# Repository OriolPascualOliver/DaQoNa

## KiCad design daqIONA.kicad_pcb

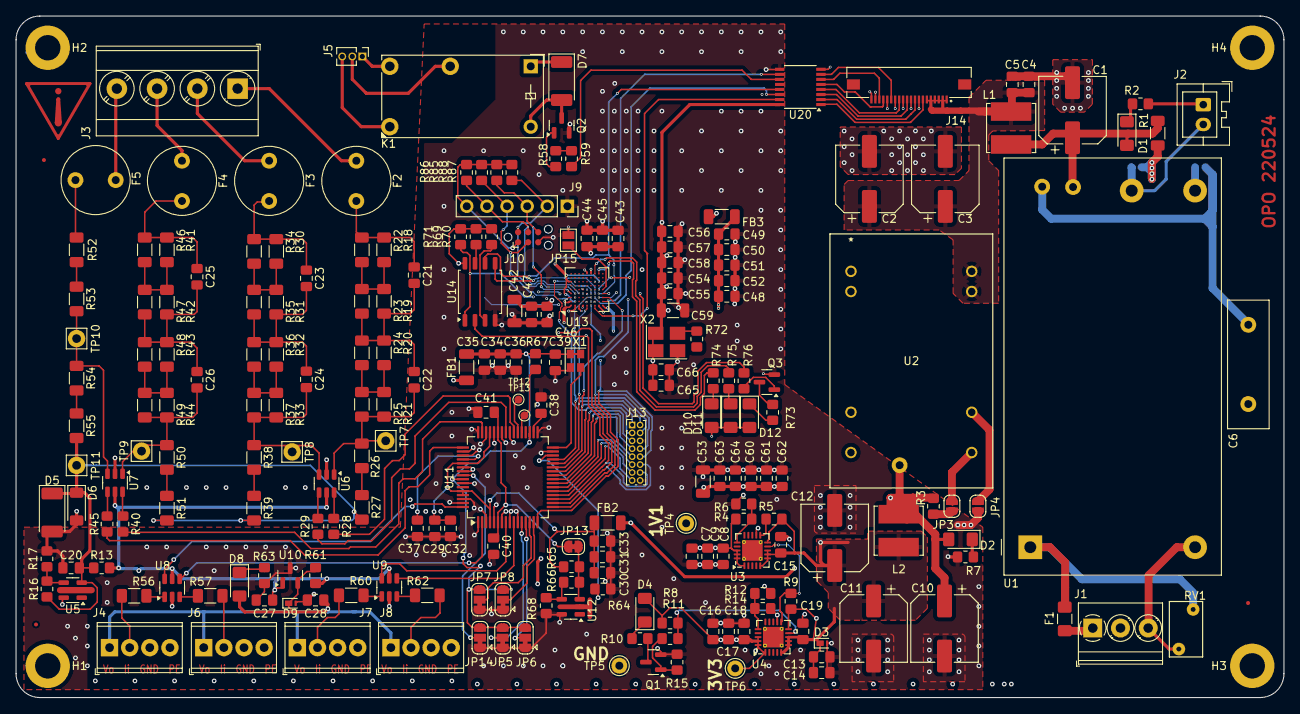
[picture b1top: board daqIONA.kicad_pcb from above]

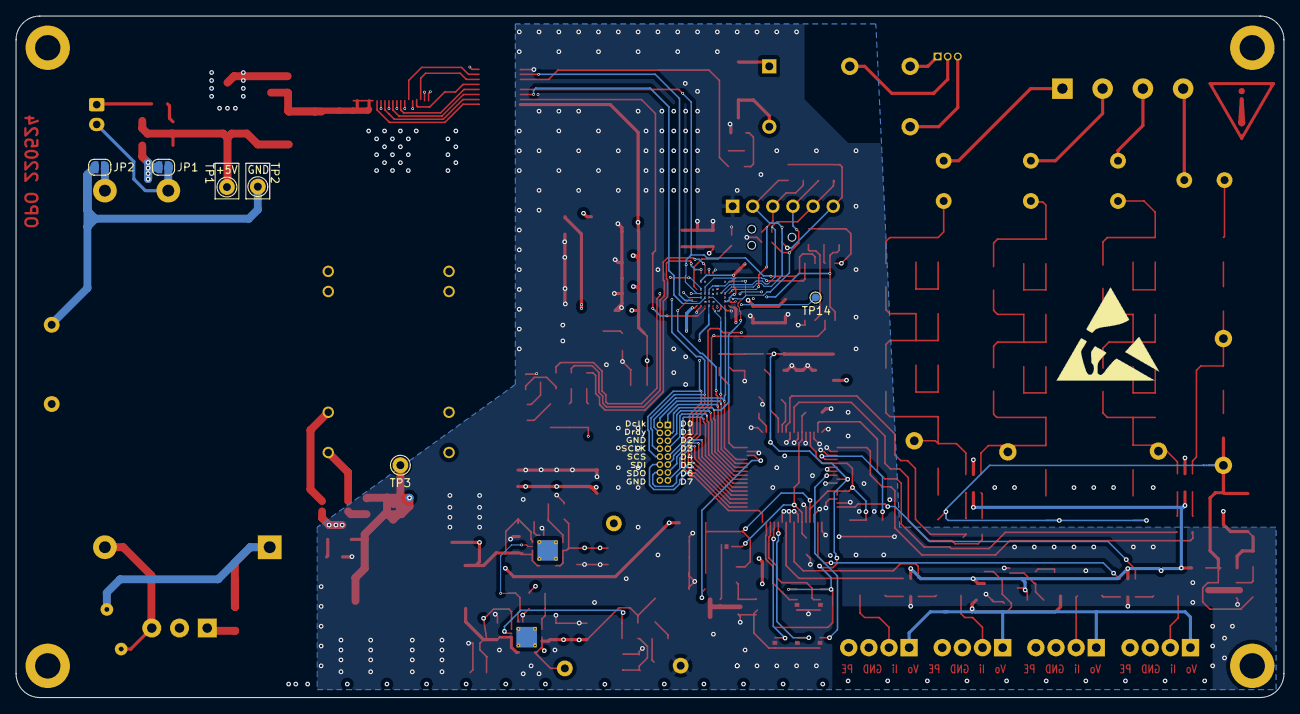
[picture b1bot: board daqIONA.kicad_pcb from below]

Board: 6 copper layers, 160.0 x 86.0 mm, 234 parts (6 on the bottom side), 144 nets.

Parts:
C1, C2, C3, C10, C11, C12: 220u; CP_Elec_8x6.9
C4, C7, C8, C13, C16, C17, C27, C28, C29, C30, C31, C34, C35, C39, C41, C44, C45, C49, C55, C56, C61, C62, C65, C66: 100n; C_0805_2012Metric_Pad1.18x1.45mm_HandSolder
C5, C14: 1n; C_0805_2012Metric_Pad1.18x1.45mm_HandSolder
C6: Cy; C_Disc_D16.0mm_W5.0mm_P10.00mm
C9, C15, C18, C19, C38: 10u; C_0805_2012Metric_Pad1.18x1.45mm_HandSolder
C20, C46, C47, C57, C58, C63, C64: 10n; C_0805_2012Metric_Pad1.18x1.45mm_HandSolder
C21, C22, C23, C24, C25, C26: 10p; C_0805_2012Metric_Pad1.18x1.45mm_HandSolder
C32, C33, C36, C37, C40, C43, C50, C51, C52, C54, C60: 1u; C_0805_2012Metric_Pad1.18x1.45mm_HandSolder
C42, C53, C59: 47u; C_1206_3216Metric
C48: 10nF; C_0805_2012Metric_Pad1.18x1.45mm_HandSolder
D1, D2, D4, D8, D10, D11, D12: LED; LED_1206_3216Metric_Pad1.42x1.75mm_HandSolder
D3: PTVS5V0Z1USK; Nexperia_DSN1608-2_1.6x0.8mm
D5, D7: D; D_MELF
D6: BZV55B2V4; D_MiniMELF
D9: PTVS7V5Z1USK; Nexperia_DSN1608-2_1.6x0.8mm
F1: Fuse; Fuse_1206_3216Metric_Pad1.42x1.75mm_HandSolder
F2, F3, F4, F5: Fuse; Fuse_Littelfuse_372_D8.50mm
FB1, FB2, FB3: FerriteBead_Small; L_1206_3216Metric_Pad1.22x1.90mm_HandSolder
FID1, FID2, FID3: Fiducial; Fiducial_0.5mm_Mask1mm
H1, H2, H3, H4: MountingHole_Pad; MountingHole_3.2mm_M3_DIN965_Pad
J1: AC PWR IN; TerminalBlock_Phoenix_PT-1,5-3-3.5-H_1x03_P3.50mm_Horizontal
J2: 5V FAN; JST_XA_B02B-XASK-1_1x02_P2.50mm_Vertical
J3: AC V MEAS; TerminalBlock_Phoenix_MKDS-3-4-5.08_1x04_P5.08mm_Horizontal
J4: Curr1 Meas; TerminalBlock_Phoenix_MPT-0,5-4-2.54_1x04_P2.54mm_Horizontal
J5: Relay OUT; PinHeader_1x03_P1.27mm_Vertical
J6: Curr2 Meas; TerminalBlock_Phoenix_MPT-0,5-4-2.54_1x04_P2.54mm_Horizontal
J7: Curr3 Meas; TerminalBlock_Phoenix_MPT-0,5-4-2.54_1x04_P2.54mm_Horizontal
J8: Curr4 Meas; TerminalBlock_Phoenix_MPT-0,5-4-2.54_1x04_P2.54mm_Horizontal
J9: Conn_01x06_Pin; PinSocket_1x06_P2.54mm_Vertical
J10: Conn_ARM_SWD_TagConnect_TC2030; Tag-Connect_TC2030-IDC-NL_2x03_P1.27mm_Vertical
J13: Conn_02x08_Odd_Even; PinHeader_2x08_P1.00mm_Vertical
J14: 687120183722
JP1, JP2, JP3, JP4: SolderJumper_2_Open; SolderJumper-2_P1.3mm_Open_RoundedPad1.0x1.5mm
JP5, JP6, JP7, JP8, JP14: SolderJumper_3_Bridged12; SolderJumper-3_P1.3mm_Bridged12_RoundedPad1.0x1.5mm
JP13: SolderJumper_2_Bridged; SolderJumper-2_P1.3mm_Bridged_RoundedPad1.0x1.5mm
JP15: RST; SolderJumper-2_P1.3mm_Open_Pad1.0x1.5mm
K1: Relay_SPDT; Relay_SPDT_Finder_32.21-x000
L1, L2: 2u2; L_Bourns_SRN6045TA
Q1, Q2, Q3: BC847; SOT-23
R1, R18, R19, R20, R21, R22, R23, R24, R25, R26, R27, R30, R31, R32, R33, R34, R35, R36, R37, R38, R39, R41, R42, R43, R44, R46, R47, R48, R49, R50, R51, R52, R53, R54, R55: R; R_1206_3216Metric_Pad1.30x1.75mm_HandSolder
R2, R7, R10, R58, R59, R63, R67, R73: 1K; R_0805_2012Metric_Pad1.20x1.40mm_HandSolder
R3, R16: 0R; R_0805_2012Metric_Pad1.20x1.40mm_HandSolder
R4: 1K87,1%; R_0805_2012Metric_Pad1.20x1.40mm_HandSolder
R5, R8, R11, R15: 10K; R_0805_2012Metric_Pad1.20x1.40mm_HandSolder
R6: 4K99,1%; R_0805_2012Metric_Pad1.20x1.40mm_HandSolder
R9, R76: 100K; R_0805_2012Metric_Pad1.20x1.40mm_HandSolder
R12: 3K57,1%; R_0805_2012Metric_Pad1.20x1.40mm_HandSolder
R13: 100R; R_0805_2012Metric_Pad1.20x1.40mm_HandSolder
R14: 1K15,1%; R_0805_2012Metric_Pad1.20x1.40mm_HandSolder
R17, R68: 300R; R_0805_2012Metric_Pad1.20x1.40mm_HandSolder
R28, R29, R40, R45: 50R; R_0805_2012Metric_Pad1.20x1.40mm_HandSolder
R56, R57, R60, R62: 1K; R_1206_3216Metric_Pad1.30x1.75mm_HandSolder
R61: 1R; R_0805_2012Metric_Pad1.20x1.40mm_HandSolder
R64: DNI; R_0805_2012Metric_Pad1.20x1.40mm_HandSolder
R65: 15R; R_0805_2012Metric_Pad1.20x1.40mm_HandSolder
R66: 190R; R_0805_2012Metric_Pad1.20x1.40mm_HandSolder
R69, R70, R71: 10k; R_0805_2012Metric_Pad1.20x1.40mm_HandSolder
R72: 33R; R_0805_2012Metric_Pad1.20x1.40mm_HandSolder
R74, R75: 1k; R_0805_2012Metric_Pad1.20x1.40mm_HandSolder
R85, R86, R87, R88: 5k; R_0805_2012Metric_Pad1.20x1.40mm_HandSolder
RV1: Varistor; RV_Disc_D7mm_W4.2mm_P5mm
TP1: 5VA; Pin_D1.0mm_L10.0mm
TP2: GND; Pin_D1.0mm_L10.0mm
TP3: 5VB; Pin_D1.0mm_L10.0mm
TP4: 1V1; Pin_D1.0mm_L10.0mm
TP5: GND3; Pin_D1.0mm_L10.0mm
TP6: 3V3; Pin_D1.0mm_L10.0mm
TP7: L1_lv; Pin_D1.1mm_L8.5mm_W2.5mm_FlatFork
TP8: L2_lv; Pin_D1.1mm_L8.5mm_W2.5mm_FlatFork
TP9: L3_lv; Pin_D1.1mm_L8.5mm_W2.5mm_FlatFork
TP10: N-lv; Pin_D1.1mm_L8.5mm_W2.5mm_FlatFork
TP11: lv_ref; Pin_D1.1mm_L8.5mm_W2.5mm_FlatFork
TP12, TP13: TestPoint; TestPoint_Pad_D1.0mm
TP14: NSTATUS; TestPoint_Pad_D1.0mm
U1: IRM-20-5; Converter_ACDC_MeanWell_IRM-20-xx_THT
U2: REC5A-0505SW/H2; DIP24_31.8X20.3X10.2_RCP
U3, U4: NCP59744; MLF-20-1EP_4x4mm_P0.5mm_EP2.6x2.6mm_ThermalVias
U5, U12: TL431DBV; SOT-23-5
U6, U7, U8, U9: USBLC6-2SC6; SOT-23-6
U10: RT9742SNGV; SOT-23
U11: AD7768BSTZ; LQFP-64_10x10mm_P0.5mm
U13: T8F81C2; BGA-81_5x5mm_Layout9x9_P0.5mm_Ball0.25mm_Pad0.2mm_NSMD
U14: W25Q128JVS; SOIC-8_5.23x5.23mm_P1.27mm
U20: ISO7761FDBQ; SSOP-16_3.9x4.9mm_P0.635mm
X1: SG-210STF; Oscillator_SMD_SeikoEpson_SG210-4Pin_2.5x2.0mm
X2: ASE-33.333MHZ-LC-T; Oscillator_SMD_Abracon_ASE-4Pin_3.2x2.5mm_HandSoldering

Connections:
+1V1: C7.1, C8.1, C9.1, C42.1, C43.1, C44.1, C45.1, C46.1, C47.1, FB3.1, R4.2, TP4.1, U3.1 (OUT), U3.18 (OUT), U3.19 (OUT), U3.20 (OUT), U13.C1 (VCC), U13.D4 (VCC), U13.E5 (VCC), U13.F2 (VCC), U13.F9 (VCC)
+3V3: C16.1, C17.1, C18.1, C53.1, C54.1, C55.1, C56.1, C57.1, C58.1, C59.1, C60.1, C61.1, C62.1, C63.1, C64.1, C65.1, C66.1, D4.2 (A), D10.2 (A), D11.2 (A), D12.2 (A), FB1.1, J9.6, J10.1 (VCC), R8.1, R12.2, R69.1, R70.1, R71.1, R85.1, R86.1, R87.1, R88.1, TP6.1, U4.1 (OUT), U4.18 (OUT), U4.19 (OUT), U4.20 (OUT), U13.A7 (VCCIO2A), U13.B2 (VCCIO1B), U13.H7 (VCCIO2B), U13.J1 (VCCIO1A), U14.8 (VCC), U20.16 (Vcc2), X2.1 (EN), X2.4 (Vdd)
+5V: C2.1, C3.1, C4.1, C5.1, J14.1, J14.2, J14.3, J14.4, J14.5, J14.6, L1.2, U2.22 (Vi+), U2.23 (Vi+)
+5VA: C11.1, C12.1, C13.1, C14.1, C15.1, C19.1, C27.1, D3.1 (K), D7.1 (K), FB2.2, K1.A1, L2.2, R5.2, R9.2, R13.1, R61.2, U3.5 (IN), U3.6 (IN), U3.7 (IN), U3.8 (IN), U3.10 (BIAS), U4.5 (IN), U4.6 (IN), U4.7 (IN), U4.8 (IN), U4.10 (BIAS), U6.5 (VBUS), U7.5 (VBUS), U8.5 (VBUS), U9.5 (VBUS), U10.1 (IN)
/(1) Power Supply/5V_PSU: J2.2, JP1.1 (A), U1.4 (+Vo)
/(1) Power Supply/Fb_{1V1}: R4.1, R6.2, U3.16 (FB)
/(1) Power Supply/Fb_{3V3}: R12.1, R14.2, U4.16 (FB)
/(1) Power Supply/PG: R8.2, R11.2, U4.9 (PG)
/(1) Power Supply/PWR_EN: R9.1, U3.9 (PG), U4.11 (EN)
/(2) Front End/Ext5V: C28.1, D8.2 (A), D9.1 (K), J4.1, J6.1, J7.1, J8.1, R61.1, U10.2 (OUT)
/(2) Front End/I1: R56.2, U8.1 (I/O1)
/(2) Front End/I2: R57.2, U8.3 (I/O2)
/(2) Front End/I3: R60.2, U9.1 (I/O1)
/(2) Front End/I4: R62.2, U9.3 (I/O2)
/(2) Front End/L1: F2.1, J3.1
/(2) Front End/L1_LV: C22.2, R21.2, R25.2, R26.1, TP7.1, U6.1 (I/O1)
/(2) Front End/L2: F3.1, J3.2
/(2) Front End/L2_LV: C24.2, R33.2, R37.2, R38.1, TP8.1, U6.3 (I/O2)
/(2) Front End/L3: F4.1, J3.3
/(2) Front End/L3_LV: C26.2, R44.2, R49.2, R50.1, TP9.1, U7.1 (I/O1)
/(2) Front End/N: F5.2, J3.4
/(2) Front End/N_LV: R53.2, R54.1, TP10.1, U7.3 (I/O2)
/(3) ADC/MODE0: JP5.2 (C), U11.12 (MODE0/GPIO0)
/(3) ADC/MODE1: JP6.2 (C), U11.13 (MODE1/GPIO1)
/(3) ADC/MODE2: JP7.2 (C), U11.14 (MODE2/GPIO2)
/(3) ADC/MODE3: JP8.2 (C), U11.15 (MODE3/GPIO3)
/(3) ADC/XTAL2: U11.32 (XTAL2/MCLK), X1.3 (OUT)
/(4) FPGA/CDONE: R76.2, U13.H5 (CDONE)
/(4) FPGA/CRST_B: JP15.2 (B), U13.J5 (CRESET_N)
/(4) FPGA/CS: U13.G1 (GPIOL_12_CTRL0), U20.15 (OUTA)
/(4) FPGA/Ext_AUX: J14.17, U20.5 (IND)
/(4) FPGA/Ext_RELAY: J14.18, U20.6 (INE)
/(4) FPGA/FPGA_HOLD: R69.2, U14.7 (IO3)
/(4) FPGA/FPGA_SS: R71.2, U13.J4 (GPIOL_01_SS_N), U14.1 (~CS)
/(4) FPGA/FPGA_TCK: J9.5, J10.4 (SWCLK), R86.2, U13.C4 (TCK)
/(4) FPGA/FPGA_TDI: J9.4, J10.3 (~RESET), R85.2, U13.A3 (TDI)
/(4) FPGA/FPGA_TDO: J9.3, J10.6 (SWO), R88.2, U13.A4 (TDO)
/(4) FPGA/FPGA_TMS: J9.2, J10.2 (SWDIO), R87.2, U13.B4 (TMS)
/(4) FPGA/FPGA~LD1: R74.2, U13.H9 (GPIOR_27)
/(4) FPGA/FPGA~LD2: R75.2, U13.G9 (GPIOR_26_CBSEL0)
/(4) FPGA/MISO: U13.J2 (GPIOL_09_CDI2), U20.10 (INF)
/(4) FPGA/MOSI: U13.G3 (GPIOL_07_CDI6), U20.14 (OUTB)
/(4) FPGA/RPI_3V3: J14.7, U20.1 (Vcc1)
/(4) FPGA/SPI0_MISO: J14.15, U20.7 (OUTF)
/(4) FPGA/SPI0_MOSI: J14.11, U20.3 (INB)
/(4) FPGA/SPI0_SCLK: J14.13, U20.4 (INC)
/(4) FPGA/SPI0_~CS: J14.9, U20.2 (INA)
/(4) FPGA/VCCA: C48.1, C49.1, C50.1, C51.1, C52.1, FB3.2, U13.A1 (VCCA_PLL)
AVDD: C29.1, C30.1, C31.1, C32.1, C33.1, FB2.1, R65.1, U11.4 (AVDD1A), U11.45 (AVDD1B), U11.53 (AVDD2B), U11.60 (AVDD2A), U11.61 (REGCAPA)
DCLK: J13.2, U11.28 (DCLK), U13.E1 (GPIOL_15_CLK1)
DOUT0: J13.1, U11.27 (DOUT0), U13.J3 (GPIOL_05_CDI5)
DOUT1: J13.3, U11.26 (DOUT1), U13.F4 (GPIOL_04_CDI0)
DOUT2: J13.5, U11.25 (DOUT2)
DOUT3: J13.7, U11.24 (DOUT3)
DOUT4: J13.9, U11.23 (DOUT4)
DOUT5: J13.11, U11.22 (DOUT5)
DOUT6: J13.13, U11.21 (DOUT6)
DOUT7: J13.15, U11.20 (DOUT7)
GND: C1.2, C2.2, C3.2, C4.2, C5.2, C6.1, J2.1, J14.8, J14.10, J14.12, J14.14, J14.16, J14.19, J14.20, JP2.2 (B), R2.2, TP2.1, U2.2 (Vi-), U2.3 (Vi-), U20.8 (GND1)
GND2: JP2.1 (A), U1.3 (-Vo)
GND3: C6.2, C7.2, C8.2, C9.2, C10.2, C11.2, C12.2, C13.2, C14.2, C15.2, C16.2, C17.2, C18.2, C19.2, C20.2, C27.2, C28.2, C29.2, C30.2, C31.2, C32.2, C33.2, C34.2, C35.2, C36.2, C37.1, C38.1, C39.2, C40.2, C41.2, C42.2, C43.2, C44.2, C45.2, C46.2, C47.2, C48.2, C49.2, C50.2, C51.2, C52.2, C53.2, C54.2, C55.2, C56.2, C57.2, C58.2, C59.2, C60.2, C61.2, C62.2, C63.2, C64.2, C65.2, C66.2, D3.2 (A), D5.2 (A), D6.2 (A), D9.2 (A), J4.3, J6.3, J7.3, J8.3, J9.1, J10.5 (GND), J13.6, J13.16, JP4.2 (B), JP5.1 (A), JP6.1 (A), JP7.1 (A), JP8.1 (A), JP14.1 (A), JP15.1 (A), Q1.2 (E), Q2.2 (E), Q3.2 (E), R6.1, R7.2, R14.1, R15.2, R17.2, R63.1, R64.1, R68.2, TP5.1, U3.12 (GND), U3.21, U4.12 (GND), U4.21, U5.5 (A), U6.2 (GND), U7.2 (GND), U8.2 (GND), U9.2 (GND), U10.3 (GND), U11.1 (AIN1-), U11.3 (AVSS1A), U11.5 (REF1-), U11.7 (AIN2-), U11.9 (AIN3-), U11.11 (FILTER/GPIO4), U11.31 (XTAL1), U11.33 (DGND), U11.40 (AIN7-), U11.42 (AIN6-), U11.44 (REF2-), U11.46 (AVSS1B), U11.48 (AIN5-), U11.50 (AIN4-), U11.51 (AVSS2B), U11.54 (AVSS), U11.55 (FORMAT1), U11.58 (CLK_SEL), U11.62 (AVSS2A), U11.63 (AIN0-), U12.5 (A), U13.A2 (GND), U13.B1 (GND), U13.B7 (GND), U13.D1 (GND), U13.D5 (GND), U13.E4 (GND), U13.E9 (GND), U13.G2 (GND), U13.G7 (GND), U13.H1 (GND), U14.4 (GND), U20.9 (GND2), X1.2 (GND), X2.2 (GND)
GNDS: C20.1, D5.1 (K), D6.1 (K), R13.2, R16.1, R27.2, R39.2, R51.2, R55.2, TP11.1, U5.3 (K)
I1_sense: U8.6 (I/O1), U11.64 (AIN0+)
I2_sense: U8.4 (I/O2), U11.2 (AIN1+)
I3_sense: U9.6 (I/O1), U11.8 (AIN2+)
I4_sense: U9.4 (I/O2), U11.10 (AIN3+)
IODD: C34.1, C35.1, C36.1, C39.1, FB1.2, JP5.3 (B), JP6.3 (B), JP7.3 (B), JP8.3 (B), JP14.3 (B), R67.2, U11.35 (IOVDD), U11.57 (~PIN/SPI), X1.1 (~ST), X1.4 (Vcc)
L1_sense: R28.2, U11.39 (AIN7+)
L2_sense: R29.2, U11.41 (AIN6+)
L3_sense: R40.2, U11.47 (AIN5+)
N_sense: R45.2, U11.49 (AIN4+)
unnamed: C21.1, F2.2, R18.1, R22.1
unnamed: C21.2, C22.1, R19.2, R20.1, R23.2, R24.1
unnamed: C23.1, F3.2, R30.1, R34.1
unnamed: C23.2, C24.1, R31.2, R32.1, R35.2, R36.1
unnamed: C25.1, F4.2, R41.1, R46.1
unnamed: C25.2, C26.1, R42.2, R43.1, R47.2, R48.1
unnamed: C1.1, D1.2 (A), L1.1, R1.2, TP1.1
unnamed: D1.1 (K), R2.1
unnamed: C10.1, D2.2 (A), L2.1, R3.2, TP3.1
unnamed: D2.1 (K), R7.1
unnamed: D4.1 (K), R10.1
unnamed: D7.2 (A), K1.A2, Q2.3 (C)
unnamed: D8.1 (K), R63.2
unnamed: D10.1 (K), R74.1
unnamed: D11.1 (K), R75.1
unnamed: D12.1 (K), R73.1
unnamed: F5.1, R52.1
unnamed: F1.1, J1.1
unnamed: J1.3, RV1.1, U1.2 (AC/N)
unnamed: J4.2, R56.1
unnamed: J5.1, K1.14
unnamed: J5.2, K1.11
unnamed: J5.3, K1.12
unnamed: J6.2, R57.1
unnamed: J7.2, R60.1
unnamed: J8.2, R62.1
unnamed: JP1.2 (B), R1.1
unnamed: JP3.1 (A), U2.14 (+Vo)
unnamed: JP3.2 (B), R3.1
unnamed: JP4.1 (A), U2.16 (-Vo)
unnamed: JP13.1 (A), R65.2, R66.1, U12.3 (K)
unnamed: JP14.2 (C), U11.56 (FORMAT0)
unnamed: Q1.1 (B), R11.1, R15.1
unnamed: Q1.3 (C), R10.2
unnamed: Q2.1 (B), R58.1
unnamed: Q3.1 (B), R76.1
unnamed: Q3.3 (C), R73.2
unnamed: R18.2, R19.1, R22.2, R23.1
unnamed: R20.2, R21.1, R24.2, R25.1
unnamed: R26.2, R27.1
unnamed: R28.1, U6.6 (I/O1)
unnamed: R29.1, U6.4 (I/O2)
unnamed: R30.2, R31.1, R34.2, R35.1
unnamed: R32.2, R33.1, R36.2, R37.1
unnamed: R38.2, R39.1
unnamed: R40.1, U7.6 (I/O1)
unnamed: R41.2, R42.1, R46.2, R47.1
unnamed: R43.2, R44.1, R48.2, R49.1
unnamed: R45.1, U7.4 (I/O2)
unnamed: R50.2, R51.1
unnamed: R52.2, R53.1
unnamed: R54.2, R55.1
unnamed: R58.2, R59.1
unnamed: F1.2, RV1.2, U1.1 (AC/L)
unnamed: R5.1, U3.11 (EN)
unnamed: R16.2, R17.1, U5.4 (REF)
unnamed: C38.2, U11.34 (DREGCAP)
unnamed: C37.2, U11.52 (REGCAPB)
unnamed: R64.2, U11.30 (~RESET)
unnamed: R67.1, TP13.1, U11.37 (~START)
unnamed: TP12.1, U11.38 (~SYNC_OUT)
unnamed: R66.2, R68.1, U12.4 (REF)
unnamed: TP14.1, U13.B3 (GPIOL_21_NSTATUS)
unnamed: R70.2, U14.3 (IO2)
unnamed: R72.1, X2.3 (OUT)
PE: H1.1, H2.1, H3.1, H4.1, J1.2, J4.4, J6.4, J7.4, J8.4
RELAY: R59.2, U20.11 (OUTE)
SCLK: J13.8, U11.17 (ST1/SCLK), U13.E2 (GPIOL_14_CLK0), U13.H4 (GPIOL_02_CCK), U14.6 (CLK), U20.13 (OUTC)
SDI: J13.12, U11.18 (DEC1/SDI), U13.G4 (GPIOL_03_CDI4), U14.5 (DI(IO0))
SDO: J13.14, U11.19 (DEC0/SDO), U13.H3 (GPIOL_06_CDI1), U14.2 (DO(IO1))
VREF: C40.1, C41.1, JP13.2 (B), U11.6 (REF1+), U11.43 (REF2+)
~DRDY: J13.4, U11.29 (~DRDY), U13.F3 (GPIOL_11_CDI3)
~SCS: J13.10, U11.16 (ST0/~CS), U13.F1 (GPIOL_13_CTRL1)

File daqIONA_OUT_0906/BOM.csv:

ID;Designator;x;Descr;Footprint;Quantity;Designation;Can be generic?;DigikeyPN;MPN;Manufacturer Descr;/uds
1;R71,R69,R70,R5,R11,R8,R15;x;0805 10K 1%;R_0805_2012Metric_Pad1.20x1.40mm_HandSolder;7;10k;Y;311-10.0KCRCT-ND;RC0805FR-0710KL;RES 10K OHM 1% 1/8W 0805;0,0131
2;FB3,FB1,FB2;x;1206 6A 50R 100Mhz FB;L_1206_3216Metric_Pad1.22x1.90mm_HandSolder;3;FerriteBead_Small;N;240-2412-1-ND;HI1206T500R-10;FERRITE BEAD 50 OHM 1206 1LN;0,0612
3;C51,C50,C40,C33,C37,C36,C32,C43,C54,C60,C52;x;0805 1u 25V XR7;C_0805_2012Metric_Pad1.18x1.45mm_HandSolder;11;1u;Y;490-10494-1-ND;GRM219R7YA105KA12D;CAP CER 1UF 35V X7R 0805;0,0752
4;R65;x;;R_0805_2012Metric_Pad1.20x1.40mm_HandSolder;1;15R;Y;YAG4833CT-ND;RT0805BRD0715RL;RES SMD 15 OHM 0.1% 1/8W 0805;0,111
6;C55,C4,C7,C49,C39,C35,C65,C29,C17,C27,C41,C44,C30,C13,C28,C62,C31,C45,C66,C56,C8,C34,C61,C16;x;;C_0805_2012Metric_Pad1.18x1.45mm_HandSolder;24;100n;Y;311-1141-1-ND;CC0805KRX7R8BB104;CAP CER 0.1UF 25V X7R 0805;0,0318
7;C63,C46,C64,C20,C57,C58,C47;x;0805 10u 25V XR7;C_0805_2012Metric_Pad1.18x1.45mm_HandSolder;7;10n;Y;311-1136-1-ND;CC0805KRX7R9BB103;CAP CER 10000PF 50V X7R 0805;0,0238
8;D10,D8,D1,D12,D2,D11,D4;x;;LED_1206_3216Metric_Pad1.42x1.75mm_HandSolder;7;LED;Y;732-4991-1-ND;150120RS75000;LED RED CLEAR 1206 SMD;0,21
9;R19,R39,R48,R41,R30,R31,R24,R25,R47,R22,R44,R50,R53,R34,R21,R54,R32,R46,R37,R18,R42,R52,R38,R20,R27,R33,R1,R26,R23,R43,R51,R35,R55,R36,R49;x;;R_1206_3216Metric_Pad1.30x1.75mm_HandSolder;35;R;DNI;;;;
10;R9,R76;x;;R_0805_2012Metric_Pad1.20x1.40mm_HandSolder;2;100K;Y;311-100KCRCT-ND;RC0805FR-07100KL;RES 100K OHM 1% 1/8W 0805;0,0123
11;R60,R57,R56,R62;x;;R_1206_3216Metric_Pad1.30x1.75mm_HandSolder;4;1K;Y;RNCP1206FTD1K00CT-ND;RNCP1206FTD1K00;RES 1K OHM 1% 1/2W 1206;0,016
12;R88,R85,R87,R86;x;;R_0805_2012Metric_Pad1.20x1.40mm_HandSolder;4;5k;Y;541-CRCW08055K00JNTACT-ND;CRCW08055K00JNTA;RES SMD 5K OHM 5% 1/8W 0805;0,044
14;C53,C42,C59;x;1206 47u 50V XR7;C_1206_3216Metric;3;47u;Y;490-GRM31CR61E476ME44KCT-ND;GRM31CR61E476ME44K;CAP CER 47UF 25V X5R 1206;0,695
16;C38,C18,C15,C9,C19;x;0805 10u 25V XR7;C_0805_2012Metric_Pad1.18x1.45mm_HandSolder;5;10u;Y;490-GRM21BZ71E106KE15LCT-ND;GRM21BZ71E106KE15L;CAP CER 10UF 25V X7R 0805;0,216
17;Q1,Q3,Q2;x;;SOT-23;3;BC847;Y;1727-2921-1-ND;BC847B,215;TRANS NPN 45V 0.1A TO236AB;0,087
18;X2;x;;Oscillator_SMD_Abracon_ASE-4Pin_3.2x2.5mm_HandSoldering;1;ASE-33.333MHZ-LC-T;N;535-ASE-33.333MHZ-E-TCT-ND;ASE-33.333MHZ-E-T;XTAL OSC XO 33.3330MHZ CMOS SMD;1,34
19;R6;x;;R_0805_2012Metric_Pad1.20x1.40mm_HandSolder;1;4K99,1%;N;YAG1921CT-ND;RT0805BRD074K99L;RES SMD 4.99K OHM 0.1% 1/8W 0805;0,111
22;R17,R68;x;;R_0805_2012Metric_Pad1.20x1.40mm_HandSolder;2;300R;Y;311-300CRCT-ND;RC0805FR-07300RL;RES 300 OHM 1% 1/8W 0805;0,0123
24;R29,R28,R40,R45,R13;x;;R_0805_2012Metric_Pad1.20x1.40mm_HandSolder;5;100R;Y;311-100HRCT-ND;RC0603FR-07100RL;RES 100 OHM 1% 1/10W 0603;0,0086
25;R58,R7,R73,R59,R67,R2,R10,R63,R75,R74;x;;R_0805_2012Metric_Pad1.20x1.40mm_HandSolder;10;1K;Y;311-1.00KCRCT-ND;RC0805FR-071KL;RES 1K OHM 1% 1/8W 0805;0,0023
26;U9,U7,U8,U6;x;;SOT-23-6;4;USBLC6-2SC6;N;497-5235-1-ND;USBLC6-2SC6;TVS DIODE 5.25VWM 17VC SOT23-6;0,252
27;U20;x;;SSOP-16_3.9x4.9mm_P0.635mm;1;ISO7761FDBQ;N;296-48813-ND;ISO7761FDBQ;DGTL ISO 3000VRMS 6CH GP 16SSOP;3,941
28;F4,F5,F3,F2;x;;Fuse_Littelfuse_372_D8.50mm;4;Fuse;N;WK4222BK-ND;37200500411;FUSE BOARD MNT 50MA 250VAC RAD;1,084
29;C3,C1,C12,C11,C2,C10;x;Electr 220uF 50V;CP_Elec_8x6.9;6;220u;N;399-A768MS227M1GLAE022CT-ND;A768MS227M1GLAE022;CAP ALUM POLY 220UF 20% 40V SMD;0,57
30;U10;x;;SOT-23;1;RT9742SNGV;N;1028-RT9742SNGVCT-ND;RT9742SNGV;IC PWR SWITCH N-CHAN 1:1 SOT23-3;0,419
31;R3,R16;x;;R_0805_2012Metric_Pad1.20x1.40mm_HandSolder;2;0R;Y;311-0.0JRCT-ND;RC0402JR-070RL;RES 0 OHM JUMPER 1/16W 0402;0,0042
33;D5,D7;x;Generic diode;D_MELF;2;D GENERIC;N;2721-SUF4001TR2-ND;SUF4001;ULTRAFAST MELF 50V 1A 50NS 175C;0,1261
34;D6;x;;D_MiniMELF;1;BZV55B2V4;N;1727-4967-1-ND;BZV55-C2V4,115;DIODE ZENER 2.4V 500MW LLDS;0,137
37;C23,C21,C25,C24,C22,C26;x;0805 10p 25V XR7;C_0805_2012Metric_Pad1.18x1.45mm_HandSolder;6;10p;DNI;;;;
41;C5,C14;x;0805 1n 25V XR7;C_0805_2012Metric_Pad1.18x1.45mm_HandSolder;2;1n;DNI;;;;
42;R66;x;;R_0805_2012Metric_Pad1.20x1.40mm_HandSolder;1;190R;DNI;;;;
43;RV1;x;;RV_Disc_D7mm_W4.2mm_P5mm;1;Varistor;DNI;;;;
44;X1;x;;Oscillator_SMD_SeikoEpson_SG210-4Pin_2.5x2.0mm;1;SG-210STF;DNI;;;;
45;L1,L2;x;;L_Bourns_SRN6045TA;2;2u2;N;SRN6045TA-6R8MCT-ND;SRN6045TA-6R8M;FIXED IND 6.8UH 3.6A 34 MOHM SMD;0,426
47;U1;x;;Converter_ACDC_MeanWell_IRM-20-xx_THT;1;IRM-20-5;DNI;1866-3042-ND;IRM-20-5;AC/DC CONVERTER 5V 20W;9,33
48;U4,U3;x;;MLF-20-1EP_4x4mm_P0.5mm_EP2.6x2.6mm_ThermalVias;2;NCP59744;N;NCP59744MN2ADJTBGOSCT-ND;NCP59744MN2ADJTBG;IC REG LINEAR POS ADJ 3A 20QFN;1,506
52;C6;x;DNI;C_Disc_D16.0mm_W5.0mm_P10.00mm;1;Cy;DNI;;;;
53;F1;x;1A 1205 Fuse;Fuse_1206_3216Metric_Pad1.42x1.75mm_HandSolder;1;Fuse;N;507-1878-1-ND;C1F 1;FUSE BRD MT 1A 125VAC 63VDC 1206;0,266
54;C48;x;0805 10n 25V XR7;C_0805_2012Metric_Pad1.18x1.45mm_HandSolder;1;10nF;Y;399-C0805X103K1RAC3316CT-ND;C0805X103K1RAC3316;CAP CER 0805 10NF 100V X7R;0,105
56;R61;x;;R_0805_2012Metric_Pad1.20x1.40mm_HandSolder;1;1R;U;311-1.00CRCT-ND;RC0805FR-071RL;RES 1 OHM 1% 1/8W 0805;0,022
58;R64;x;;R_0805_2012Metric_Pad1.20x1.40mm_HandSolder;1;DNI;DNI;;;;
60;U12,U5;x;;SOT-23-5;2;TL431DBV;N;296-17623-1-ND;TL431BQDBZR;IC VREF SHUNT ADJ 0.5% SOT23-3;0,39
61;U11;x;DNI;LQFP-64_10x10mm_P0.5mm;1;AD7768BSTZ;DNI;505-AD7768BSTZ-ND;AD7768BSTZ;IC ADC 24BIT SIGMA-DELTA 64LQFP;39,241
65;U2;x;;DIP24_31.8X20.3X10.2_RCP;1;REC5A-0505SW/H2;N;945-3011-ND;REC5A-0505SW/H2;DC DC CONVERTER 5V 5W;13,29
66;R12;x;;R_0805_2012Metric_Pad1.20x1.40mm_HandSolder;1;3K57,1%;N;10-ERA-6AEB3571VCT-ND;ERA-6AEB3571V;RES SMD 3.57K OHM 0.1% 1/8W 0805;0,091
67;U13;x;;BGA-81_5x5mm_Layout9x9_P0.5mm_Ball0.25mm_Pad0.2mm_NSMD;1;T8F81C2;N;2134-T8F81C2CT-ND;T8F81C2;IC FPGA TRION T8 55 I/O 81FBGA;6,66
68;R14;x;;R_0805_2012Metric_Pad1.20x1.40mm_HandSolder;1;1K15,1%;N;P1.15KDACT-ND;ERA-6AEB1151V;RES SMD 1.15K OHM 0.1% 1/8W 0805;0,091
69;D9;x;;Nexperia_DSN1608-2_1.6x0.8mm;1;PTVS7V5Z1USK;N;1727-2743-1-ND;PTVS7V5Z1USKYL;TVS DIODE 7.5VWM 13.5VC DSN1608;0,295
71;D3;x;;Nexperia_DSN1608-2_1.6x0.8mm;1;PTVS5V0Z1USK;N;1727-2742-1-ND;PTVS5V0Z1USKYL;TVS DIODE 5VWM 12VC DSN1608-2;0,207
72;R4;x;;R_0805_2012Metric_Pad1.20x1.40mm_HandSolder;1;1K87,1%;N;P1.87KDACT-ND;ERA-6AEB1871V;RES SMD 1.87K OHM 0.1% 1/8W 0805;0,091
73;R72;x;;R_0805_2012Metric_Pad1.20x1.40mm_HandSolder;1;33R;N;RR12Q33DCT-ND;RR1220Q-330-D;RES SMD 33 OHM 0.5% 1/10W 0805;0,0377
74;U14;x;;SOIC-8_5.23x5.23mm_P1.27mm;1;W25Q128JVS;N;W25Q128JVSIQ-ND;W25Q128JVSIQ;IC FLASH 128MBIT SPI/QUAD 8SOIC;1,6
77;K1;x;DNI;Relay_SPDT_Finder_32.21-x000;1;Relay_SPDT;DNI;;;;
;;x;;;;;;;;;
;;x;;;;;;;;;

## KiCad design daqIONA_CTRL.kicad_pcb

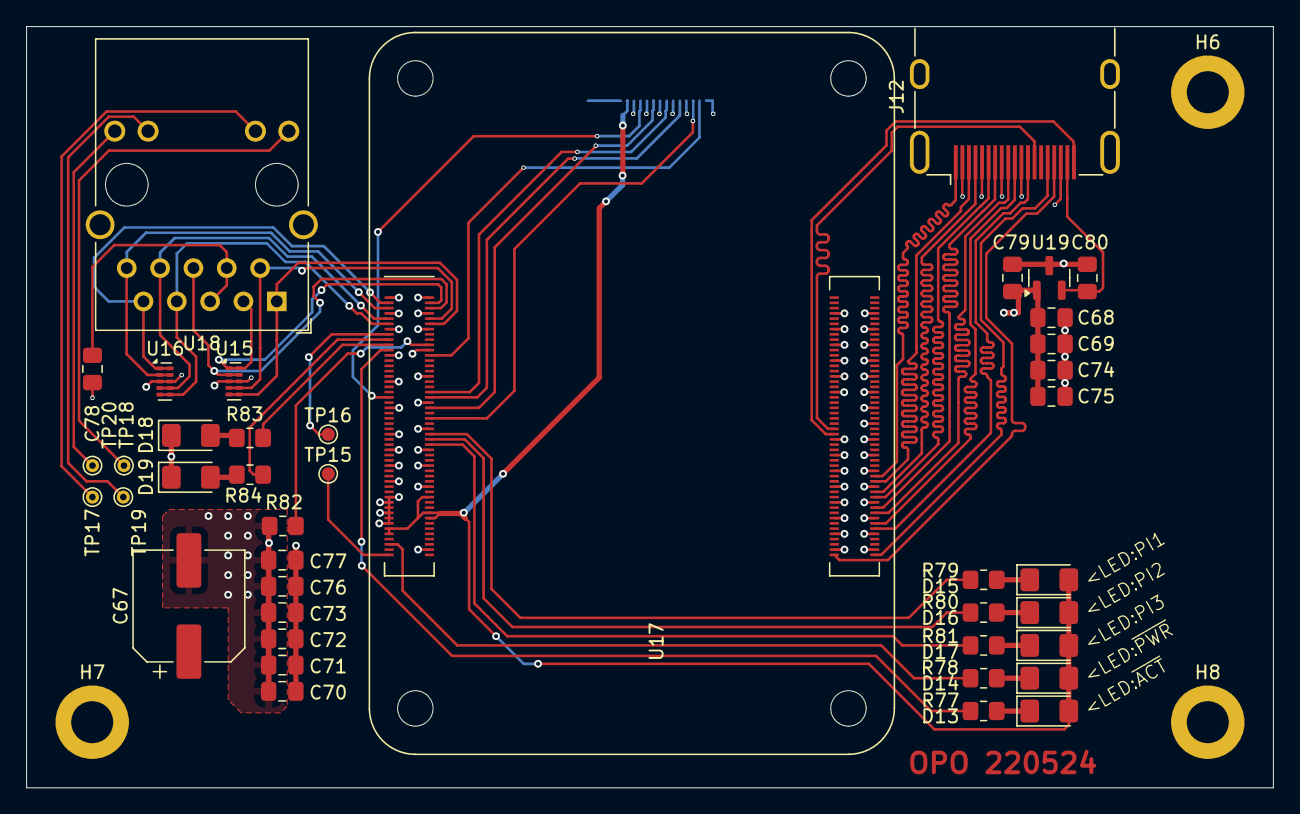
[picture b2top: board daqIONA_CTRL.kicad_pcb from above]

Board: 4 copper layers, 95.0 x 58.0 mm, 45 parts (1 on the bottom side), 52 nets.

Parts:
C67: 220u; CP_Elec_8x6.9
C68, C69, C70, C71, C72, C73, C78, C79, C80: 100n; C_0805_2012Metric_Pad1.18x1.45mm_HandSolder
C74, C75, C76, C77: 1n; C_0805_2012Metric_Pad1.18x1.45mm_HandSolder
D13, D14, D15, D16, D17, D18, D19: LED; LED_1206_3216Metric_Pad1.42x1.75mm_HandSolder
H6, H7, H8: MountingHole_Pad; MountingHole_3.2mm_M3_DIN965_Pad
J12: HDMI_A_1.4; HDMI_A_Molex_208658-1001_Horizontal
J15: 687120183722
R77, R78, R79, R80, R81, R83, R84: 1k; R_0805_2012Metric_Pad1.20x1.40mm_HandSolder
R82: DNI; R_0805_2012Metric_Pad1.20x1.40mm_HandSolder
TP15, TP16: TestPoint; TestPoint_Pad_D1.0mm
TP17, TP18, TP19, TP20: TestPoint; TestPoint_THTPad_D1.0mm_Drill0.5mm
U15, U16: TPD4EUSB30; USON-10_2.5x1.0mm_P0.5mm
U17: CM4102008; Raspberry-Pi-4-Compute-Module
U18: MagJack-A70-112-331N126; RJ45_Wuerth_7499111446_Horizontal
U19: RT9742SNGV; SOT-23

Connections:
+5V: C67.1, C68.1, C69.1, C70.1, C71.1, C72.1, C73.1, C74.1, C75.1, C76.1, C77.1, C79.1, D18.1 (K), D19.1 (K), J15.1, J15.2, J15.3, J15.4, J15.5, J15.6, U17.77 (+5V(INPUT)), U17.79 (+5V(INPUT)), U17.81 (+5V(INPUT)), U17.83 (+5V(INPUT)), U17.85 (+5V(INPUT)), U17.87 (+5V(INPUT)), U19.1 (IN)
/(5) RPI SbC/CEC: J12.13 (CEC), U17.151 (HDMI0_CEC)
/(5) RPI SbC/CLK_N: J12.12 (CK-), U17.190 (HDMI0_CLK_N)
/(5) RPI SbC/CLK_P: J12.10 (CK+), U17.188 (HDMI0_CLK_P)
/(5) RPI SbC/ETH_LEDG: R83.1, U17.19 (ETHERNET_~LED1)
/(5) RPI SbC/ETH_LEDY: R84.1, U17.17 (ETHERNET_~LED2)
/(5) RPI SbC/Ext_AUX: J15.17, U17.48 (GPIO27)
/(5) RPI SbC/Ext_RELAY: J15.18, U17.24 (GPIO26)
/(5) RPI SbC/HDMI_5V: C80.1, J12.18 (+5V), U19.2 (OUT)
/(5) RPI SbC/HotPlug: J12.19 (HPD/HEAC-), U17.153 (HDMI0_HOTPLUG)
/(5) RPI SbC/LED_PI1: R81.2, U17.58 (GPIO2)
/(5) RPI SbC/LED_PI2: R80.2, U17.56 (GPIO3)
/(5) RPI SbC/LED_PI3: R79.2, U17.54 (GPIO4)
/(5) RPI SbC/LED~ACT: R77.2, U17.21 (PI_~LED_ACTIVITY)
/(5) RPI SbC/LED~PWR: R78.2, U17.95 (PI_LED_~PWR)
/(5) RPI SbC/RPI_3V3: D13.2 (A), D14.2 (A), D15.2 (A), D16.2 (A), D17.2 (A), J15.7, U17.78 (GPIO_VREF), U17.84 (CM4_3.3V(OUTPUT)), U17.86 (CM4_3.3V(OUTPUT)), U17.89 (WL_~DISABLE), U17.91 (BT_~DISABLE)
/(5) RPI SbC/SCL: J12.15 (SCL), U17.200 (HDMI0_SCL)
/(5) RPI SbC/SDA: J12.16 (SDA), U17.199 (HDMI0_SDA)
/(5) RPI SbC/SPI0_MISO: J15.15, U17.40 (GPIO9)
/(5) RPI SbC/SPI0_MOSI: J15.11, U17.44 (GPIO10)
/(5) RPI SbC/SPI0_SCLK: J15.13, U17.38 (GPIO11)
/(5) RPI SbC/SPI0_~CS: J15.9, U17.39 (GPIO8)
/(5) RPI SbC/TR0_TAP: TP18.1, U18.11 (VC1)
/(5) RPI SbC/TR1_TAP: TP17.1, U18.12 (VC2)
/(5) RPI SbC/TR2_TAP: TP19.1, U18.13 (VC3)
/(5) RPI SbC/TR3_TAP: TP20.1, U18.14 (VC4)
/(5) RPI SbC/TRD0_N: U15.4 (D2+), U15.7, U17.10 (ETHERNET_PAIR0_N), U18.2 (TRD0-)
/(5) RPI SbC/TRD0_P: U15.5 (D2-), U15.6, U17.12 (ETHERNET_PAIR0_P), U18.1 (TRD0+)
/(5) RPI SbC/TRD1_N: U15.2 (D1-), U15.9, U17.6 (ETHERNET_PAIR1_N), U18.6 (TRD1-)
/(5) RPI SbC/TRD1_P: U15.1 (D1+), U15.10, U17.4 (ETHERNET_PAIR1_P), U18.3 (TRD1+)
/(5) RPI SbC/TRD2_N: U16.4 (D2+), U16.7, U17.9 (ETHERNET_PAIR2_N), U18.8 (TRD2-)
/(5) RPI SbC/TRD2_P: U16.5 (D2-), U16.6, U17.11 (ETHERNET_PAIR2_P), U18.7 (TRD2+)
/(5) RPI SbC/TRD3_N: U16.2 (D1-), U16.9, U17.5 (ETHERNET_PAIR3_N), U18.10 (TRD3-)
/(5) RPI SbC/TRD3_P: U16.1 (D1+), U16.10, U17.3 (ETHERNET_PAIR3_P), U18.9 (TRD3+)
/(5) RPI SbC/TX0_N: J12.9 (D0-), U17.184 (HDMI0_TX0_N)
/(5) RPI SbC/TX0_P: J12.7 (D0+), U17.182 (HDMI0_TX0_P)
/(5) RPI SbC/TX1_N: J12.6 (D1-), U17.178 (HDMI0_TX1_N)
/(5) RPI SbC/TX1_P: J12.4 (D1+), U17.176 (HDMI0_TX1_P)
/(5) RPI SbC/TX2_N: J12.3 (D2-), U17.172 (HDMI0_TX2_N)
/(5) RPI SbC/TX2_P: J12.1 (D2+), U17.170 (HDMI0_TX2_P)
GND: C67.2, C68.2, C69.2, C70.2, C71.2, C72.2, C73.2, C74.2, C75.2, C76.2, C77.2, C78.2, C79.2, C80.2, H6.1, H7.1, H8.1, J12.2 (D2S), J12.5 (D1S), J12.8 (D0S), J12.11 (CKS), J12.17 (GND), J12.SH, J15.8, J15.10, J15.12, J15.14, J15.16, J15.19, J15.20, R82.2, U15.3 (GND), U15.8 (GND), U16.3 (GND), U16.8 (GND), U17.1 (GND), U17.2 (GND), U17.7 (GND), U17.8 (GND), U17.13 (GND), U17.14 (GND), U17.22 (GND), U17.23 (GND), U17.32 (GND), U17.33 (GND), U17.42 (GND), U17.43 (GND), U17.52 (GND), U17.53 (GND), U17.59 (GND), U17.60 (GND), U17.65 (GND), U17.66 (GND), U17.71 (GND), U17.74 (GND), U17.98 (GND), U17.107 (GND), U17.108 (GND), U17.113 (GND), U17.114 (GND), U17.119 (GND), U17.120 (GND), U17.125 (GND), U17.126 (GND), U17.131 (GND), U17.132 (GND), U17.137 (GND), U17.138 (GND), U17.144 (GND), U17.150 (GND), U17.155 (GND), U17.156 (GND), U17.161 (GND), U17.162 (GND), U17.167 (GND), U17.168 (GND), U17.173 (GND), U17.174 (GND), U17.179 (GND), U17.180 (GND), U17.185 (GND), U17.186 (GND), U17.191 (GND), U17.192 (GND), U17.197 (GND), U17.198 (GND), U19.3 (GND)
unnamed: C78.1, U18.4 (CT), U18.5 (CT)
unnamed: D13.1 (K), R77.1
unnamed: D14.1 (K), R78.1
unnamed: D15.1 (K), R79.1
unnamed: D16.1 (K), R80.1
unnamed: D17.1 (K), R81.1
unnamed: D18.2 (A), R83.2
unnamed: D19.2 (A), R84.2
unnamed: R82.1, U17.20 (EEPROM_~WP)
unnamed: TP16.1, U17.15 (ETHERNET_~LED3)
unnamed: TP15.1, U17.99 (GLOBAL_EN)
